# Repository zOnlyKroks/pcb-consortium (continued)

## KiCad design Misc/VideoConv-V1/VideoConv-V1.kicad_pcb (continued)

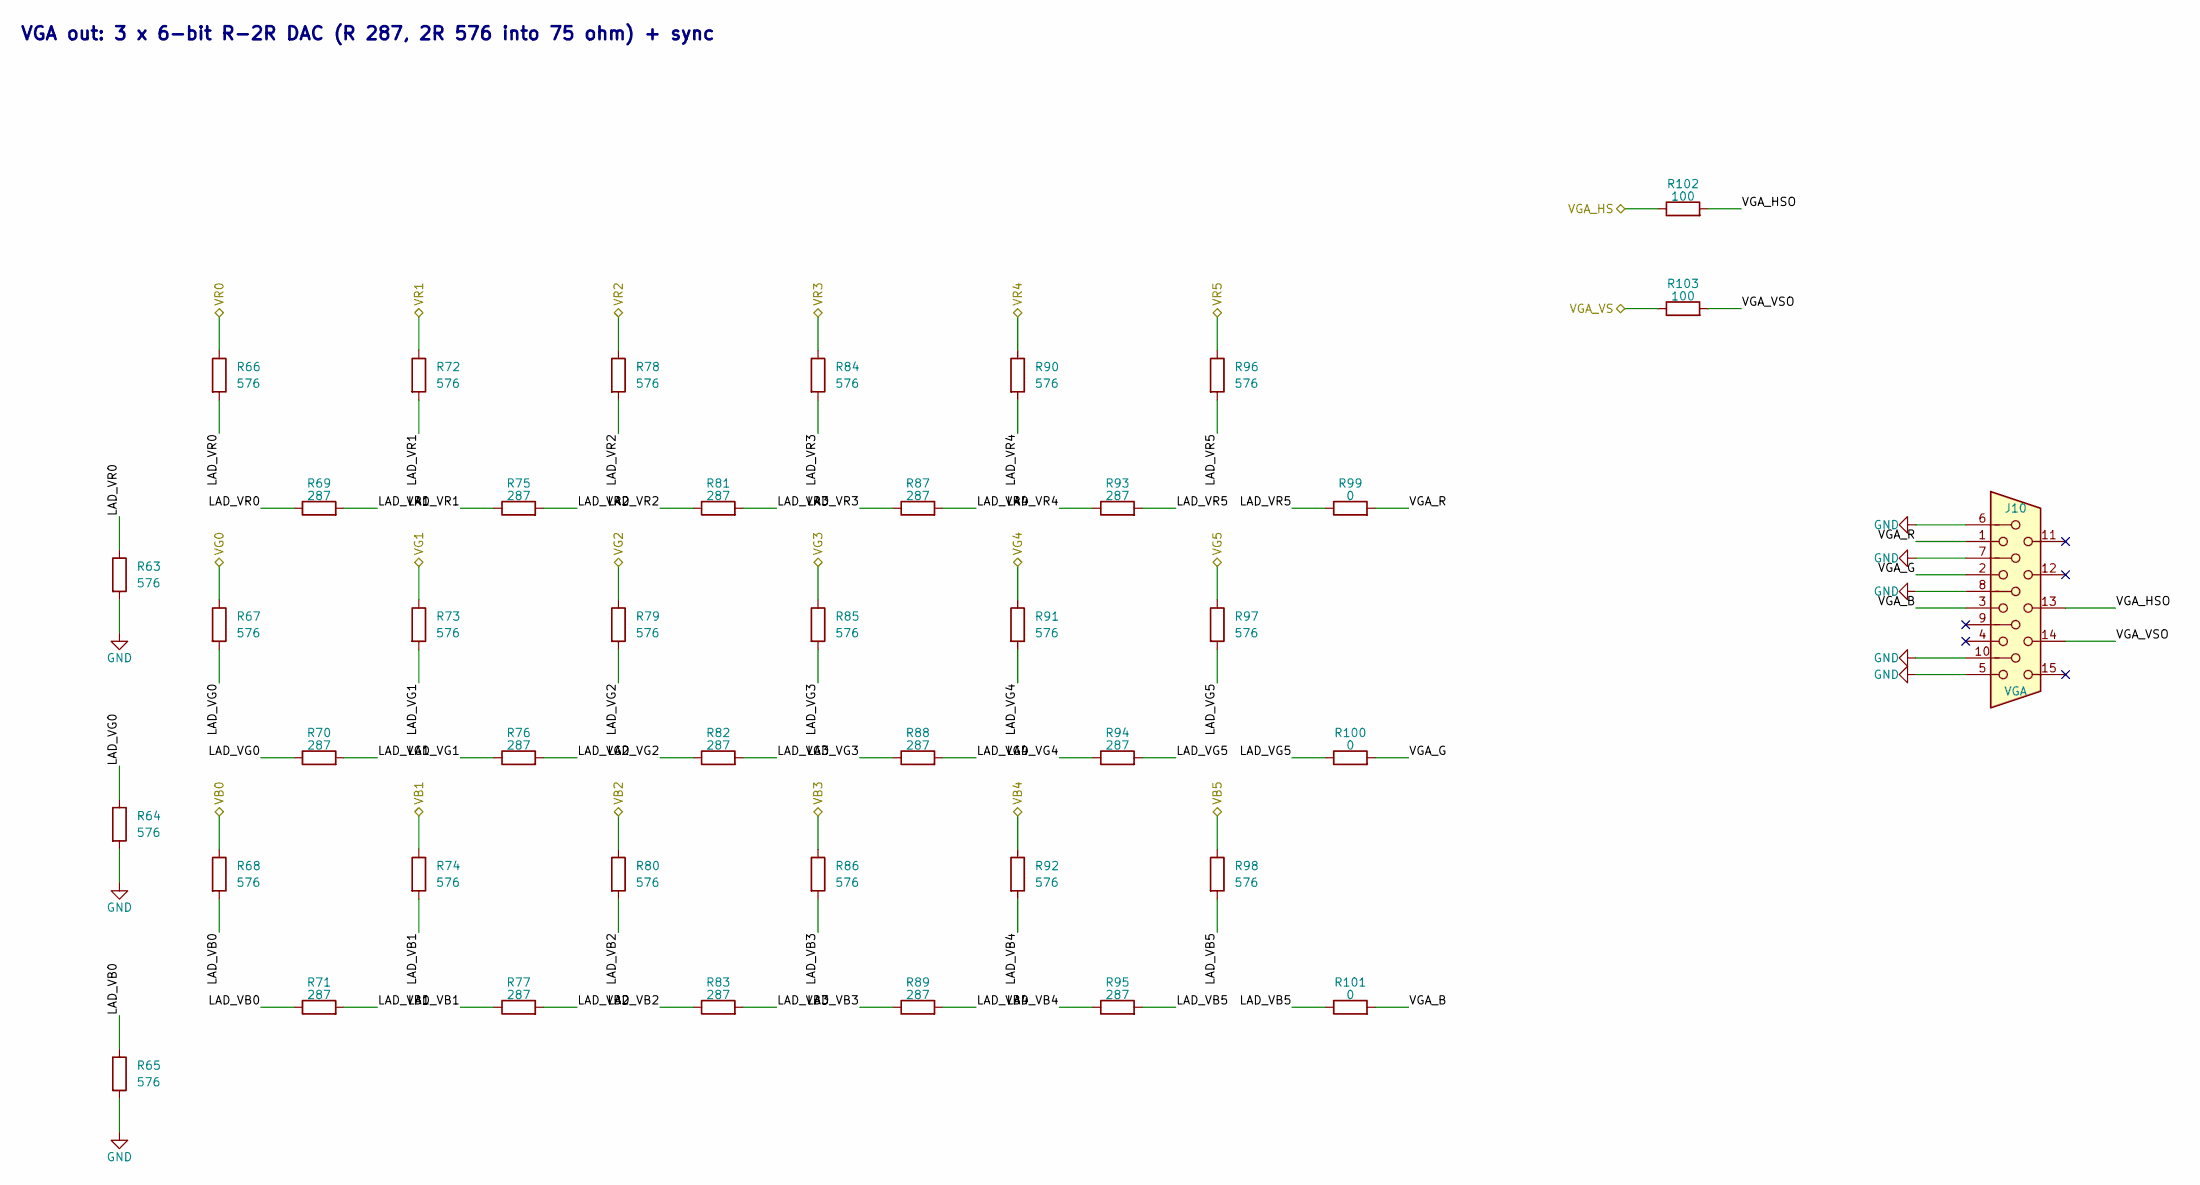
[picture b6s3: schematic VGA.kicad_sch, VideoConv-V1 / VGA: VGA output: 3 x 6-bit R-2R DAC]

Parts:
J10: VGA; DSUB-15-HD_Socket_Horizontal_P2.29x1.90mm_EdgePinOffset3.03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; LCSC Part # C5172168
R63, R64, R65, R66, R67, R68, R72, R73, R74, R78, R79, R80, R84, R85, R86, R90, R91, R92, R96, R97, R98: 576; R_0603_1608Metric; Tolerance 1%; LCSC Part # C245982
R69, R70, R71, R75, R76, R77, R81, R82, R83, R87, R88, R89, R93, R94, R95: 287; R_0603_1608Metric; Tolerance 1%; LCSC Part # C22929
R99, R100, R101: 0; R_0603_1608Metric; LCSC Part # C21189
R102, R103: 100; R_0603_1608Metric; LCSC Part # C22775

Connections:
/VB0: R68.1; also elsewhere on the board
/VB1: R74.1; also elsewhere on the board
/VB2: R80.1; also elsewhere on the board
/VB3: R86.1; also elsewhere on the board
/VB4: R92.1; also elsewhere on the board
/VB5: R98.1; also elsewhere on the board
/VG0: R67.1; also elsewhere on the board
/VG1: R73.1; also elsewhere on the board
/VG2: R79.1; also elsewhere on the board
/VG3: R85.1; also elsewhere on the board
/VG4: R91.1; also elsewhere on the board
/VG5: R97.1; also elsewhere on the board
/VGA/LAD_VB0: R65.1, R68.2, R71.1
/VGA/LAD_VB1: R71.2, R74.2, R77.1
/VGA/LAD_VB2: R77.2, R80.2, R83.1
/VGA/LAD_VB3: R83.2, R86.2, R89.1
/VGA/LAD_VB4: R89.2, R92.2, R95.1
/VGA/LAD_VB5: R95.2, R98.2, R101.1
/VGA/LAD_VG0: R64.1, R67.2, R70.1
/VGA/LAD_VG1: R70.2, R73.2, R76.1
/VGA/LAD_VG2: R76.2, R79.2, R82.1
/VGA/LAD_VG3: R82.2, R85.2, R88.1
/VGA/LAD_VG4: R88.2, R91.2, R94.1
/VGA/LAD_VG5: R94.2, R97.2, R100.1
/VGA/LAD_VR0: R63.1, R66.2, R69.1
/VGA/LAD_VR1: R69.2, R72.2, R75.1
/VGA/LAD_VR2: R75.2, R78.2, R81.1
/VGA/LAD_VR3: R81.2, R84.2, R87.1
/VGA/LAD_VR4: R87.2, R90.2, R93.1
/VGA/LAD_VR5: R93.2, R96.2, R99.1
/VGA/VGA_B: J10.3, R101.2
/VGA/VGA_G: J10.2, R100.2
/VGA/VGA_HSO: J10.13, R102.2
/VGA/VGA_R: J10.1, R99.2
/VGA/VGA_VSO: J10.14, R103.2
/VGA_HS: R102.1; also elsewhere on the board
/VGA_VS: R103.1; also elsewhere on the board
/VR0: R66.1; also elsewhere on the board
/VR1: R72.1; also elsewhere on the board
/VR2: R78.1; also elsewhere on the board
/VR3: R84.1; also elsewhere on the board
/VR4: R90.1; also elsewhere on the board
/VR5: R96.1; also elsewhere on the board
GND: J10.5, J10.6, J10.7, J10.8, J10.10, R63.2, R64.2, R65.2; also elsewhere on the board

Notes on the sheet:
VGA out: 3 x 6-bit R-2R DAC (R 287, 2R 576 into 75 ohm) + sync

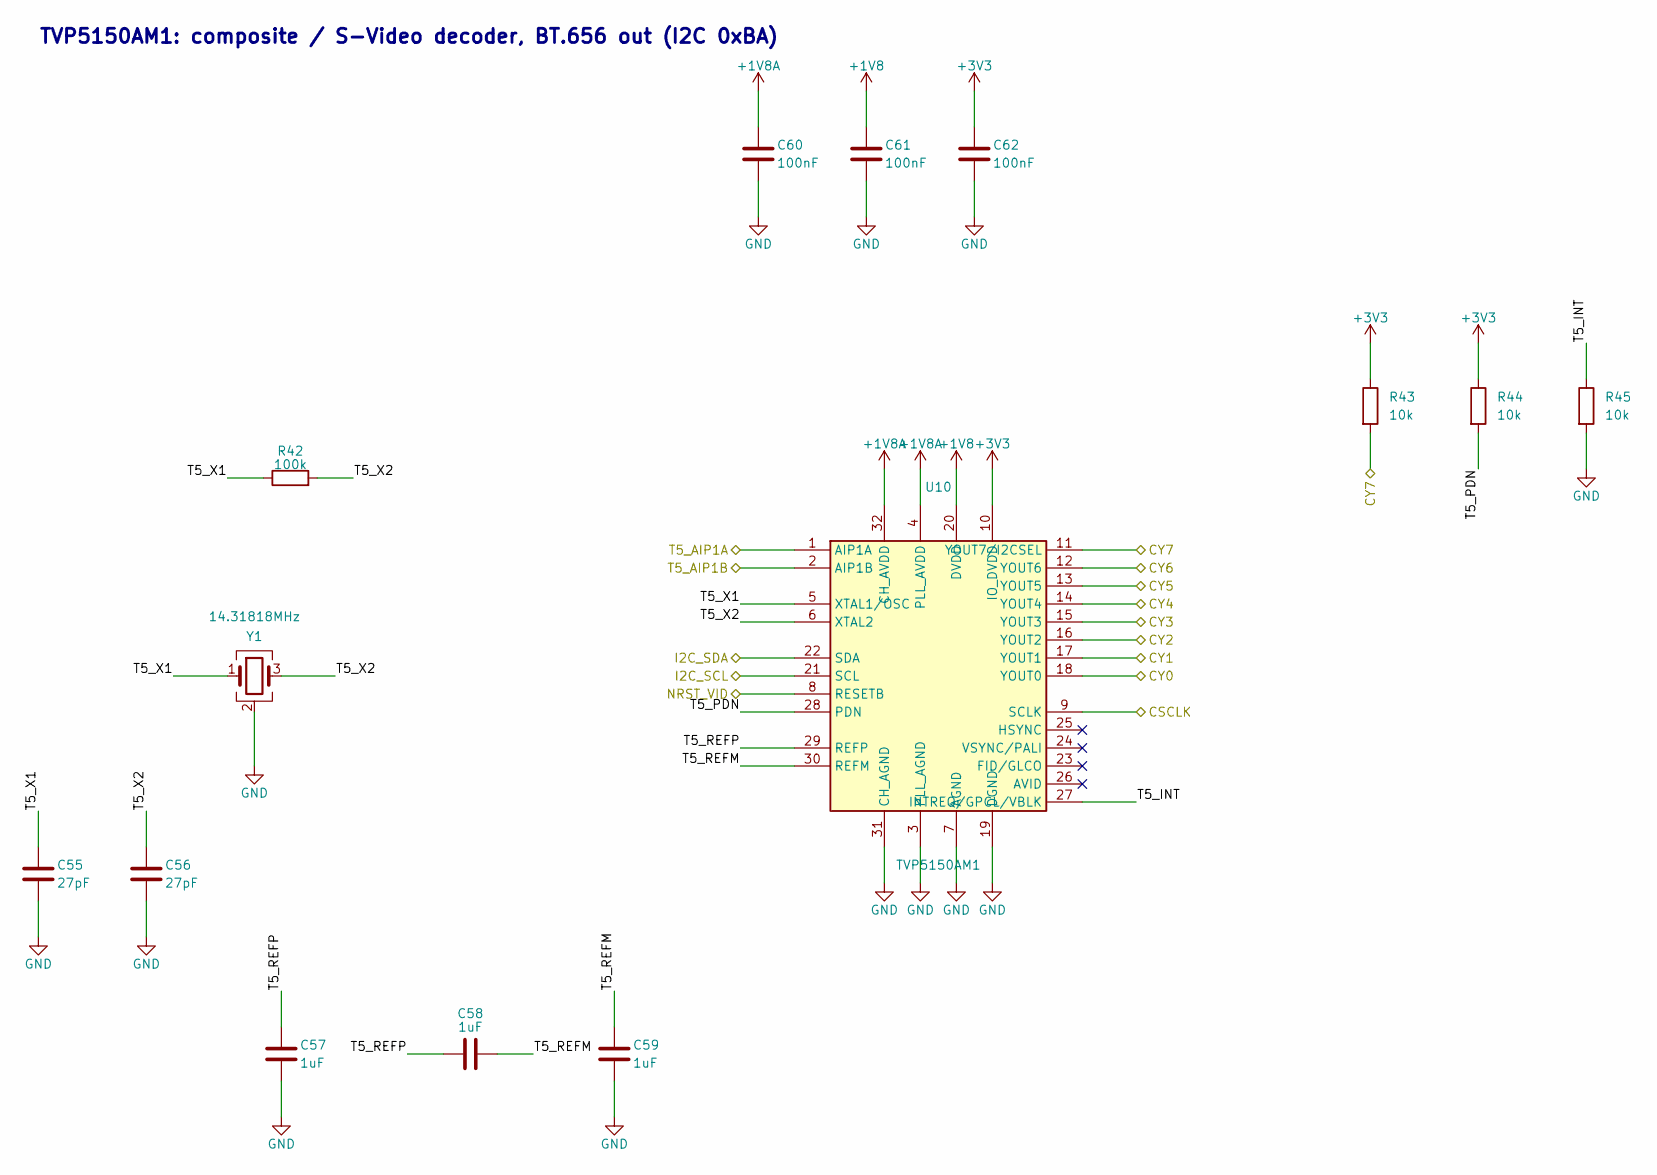
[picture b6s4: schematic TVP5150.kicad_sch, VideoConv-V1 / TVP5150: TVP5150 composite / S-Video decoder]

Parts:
C55, C56: 27pF; C_0603_1608Metric; LCSC Part # C1656
C57, C58, C59: 1uF; C_0603_1608Metric; LCSC Part # C29936
C60, C61, C62: 100nF; C_0603_1608Metric; LCSC Part # C1591
R42: 100k; R_0603_1608Metric; LCSC Part # C25803
R43, R44, R45: 10k; R_0603_1608Metric; LCSC Part # C25804
U10: TVP5150AM1; TQFP-32_7x7mm_P0.8mm; MPN TVP5150AM1PBS; LCSC Part # C3824301
Y1: 14.31818MHz; Crystal_SMD_3225-4Pin_3.2x2.5mm; LCSC Part # C6531315

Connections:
+1V8: C61.1, U10.20 (DVDD); also elsewhere on the board
+1V8A: C60.1, U10.4 (PLL_AVDD), U10.32 (CH_AVDD); also elsewhere on the board
+3V3: C62.1, R43.1, R44.1, U10.10 (IO_DVDD); also elsewhere on the board
/CSCLK: U10.9 (SCLK); also elsewhere on the board
/CY0: U10.18 (YOUT0); also elsewhere on the board
/CY1: U10.17 (YOUT1); also elsewhere on the board
/CY2: U10.16 (YOUT2); also elsewhere on the board
/CY3: U10.15 (YOUT3); also elsewhere on the board
/CY4: U10.14 (YOUT4); also elsewhere on the board
/CY5: U10.13 (YOUT5); also elsewhere on the board
/CY6: U10.12 (YOUT6); also elsewhere on the board
/CY7: R43.2, U10.11 (YOUT7/I2CSEL); also elsewhere on the board
/I2C_SCL: U10.21 (SCL); also elsewhere on the board
/I2C_SDA: U10.22 (SDA); also elsewhere on the board
/NRST_VID: U10.8 (RESETB); also elsewhere on the board
/T5_AIP1A: U10.1 (AIP1A); also elsewhere on the board
/T5_AIP1B: U10.2 (AIP1B); also elsewhere on the board
/TVP5150/T5_INT: R45.1, U10.27 (INTREQ/GPCL/VBLK)
/TVP5150/T5_PDN: R44.2, U10.28 (PDN)
/TVP5150/T5_REFM: C58.2, C59.1, U10.30 (REFM)
/TVP5150/T5_REFP: C57.1, C58.1, U10.29 (REFP)
/TVP5150/T5_X1: C55.1, R42.1, U10.5 (XTAL1/OSC), Y1.1
/TVP5150/T5_X2: C56.1, R42.2, U10.6 (XTAL2), Y1.3
GND: C55.2, C56.2, C57.2, C59.2, C60.2, C61.2, C62.2, R45.2, U10.3 (PLL_AGND), U10.7 (AGND), U10.19 (DGND), U10.31 (CH_AGND), Y1.2 (G), Y1.4 (G); also elsewhere on the board

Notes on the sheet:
TVP5150AM1: composite / S-Video decoder, BT.656 out (I2C 0xBA)

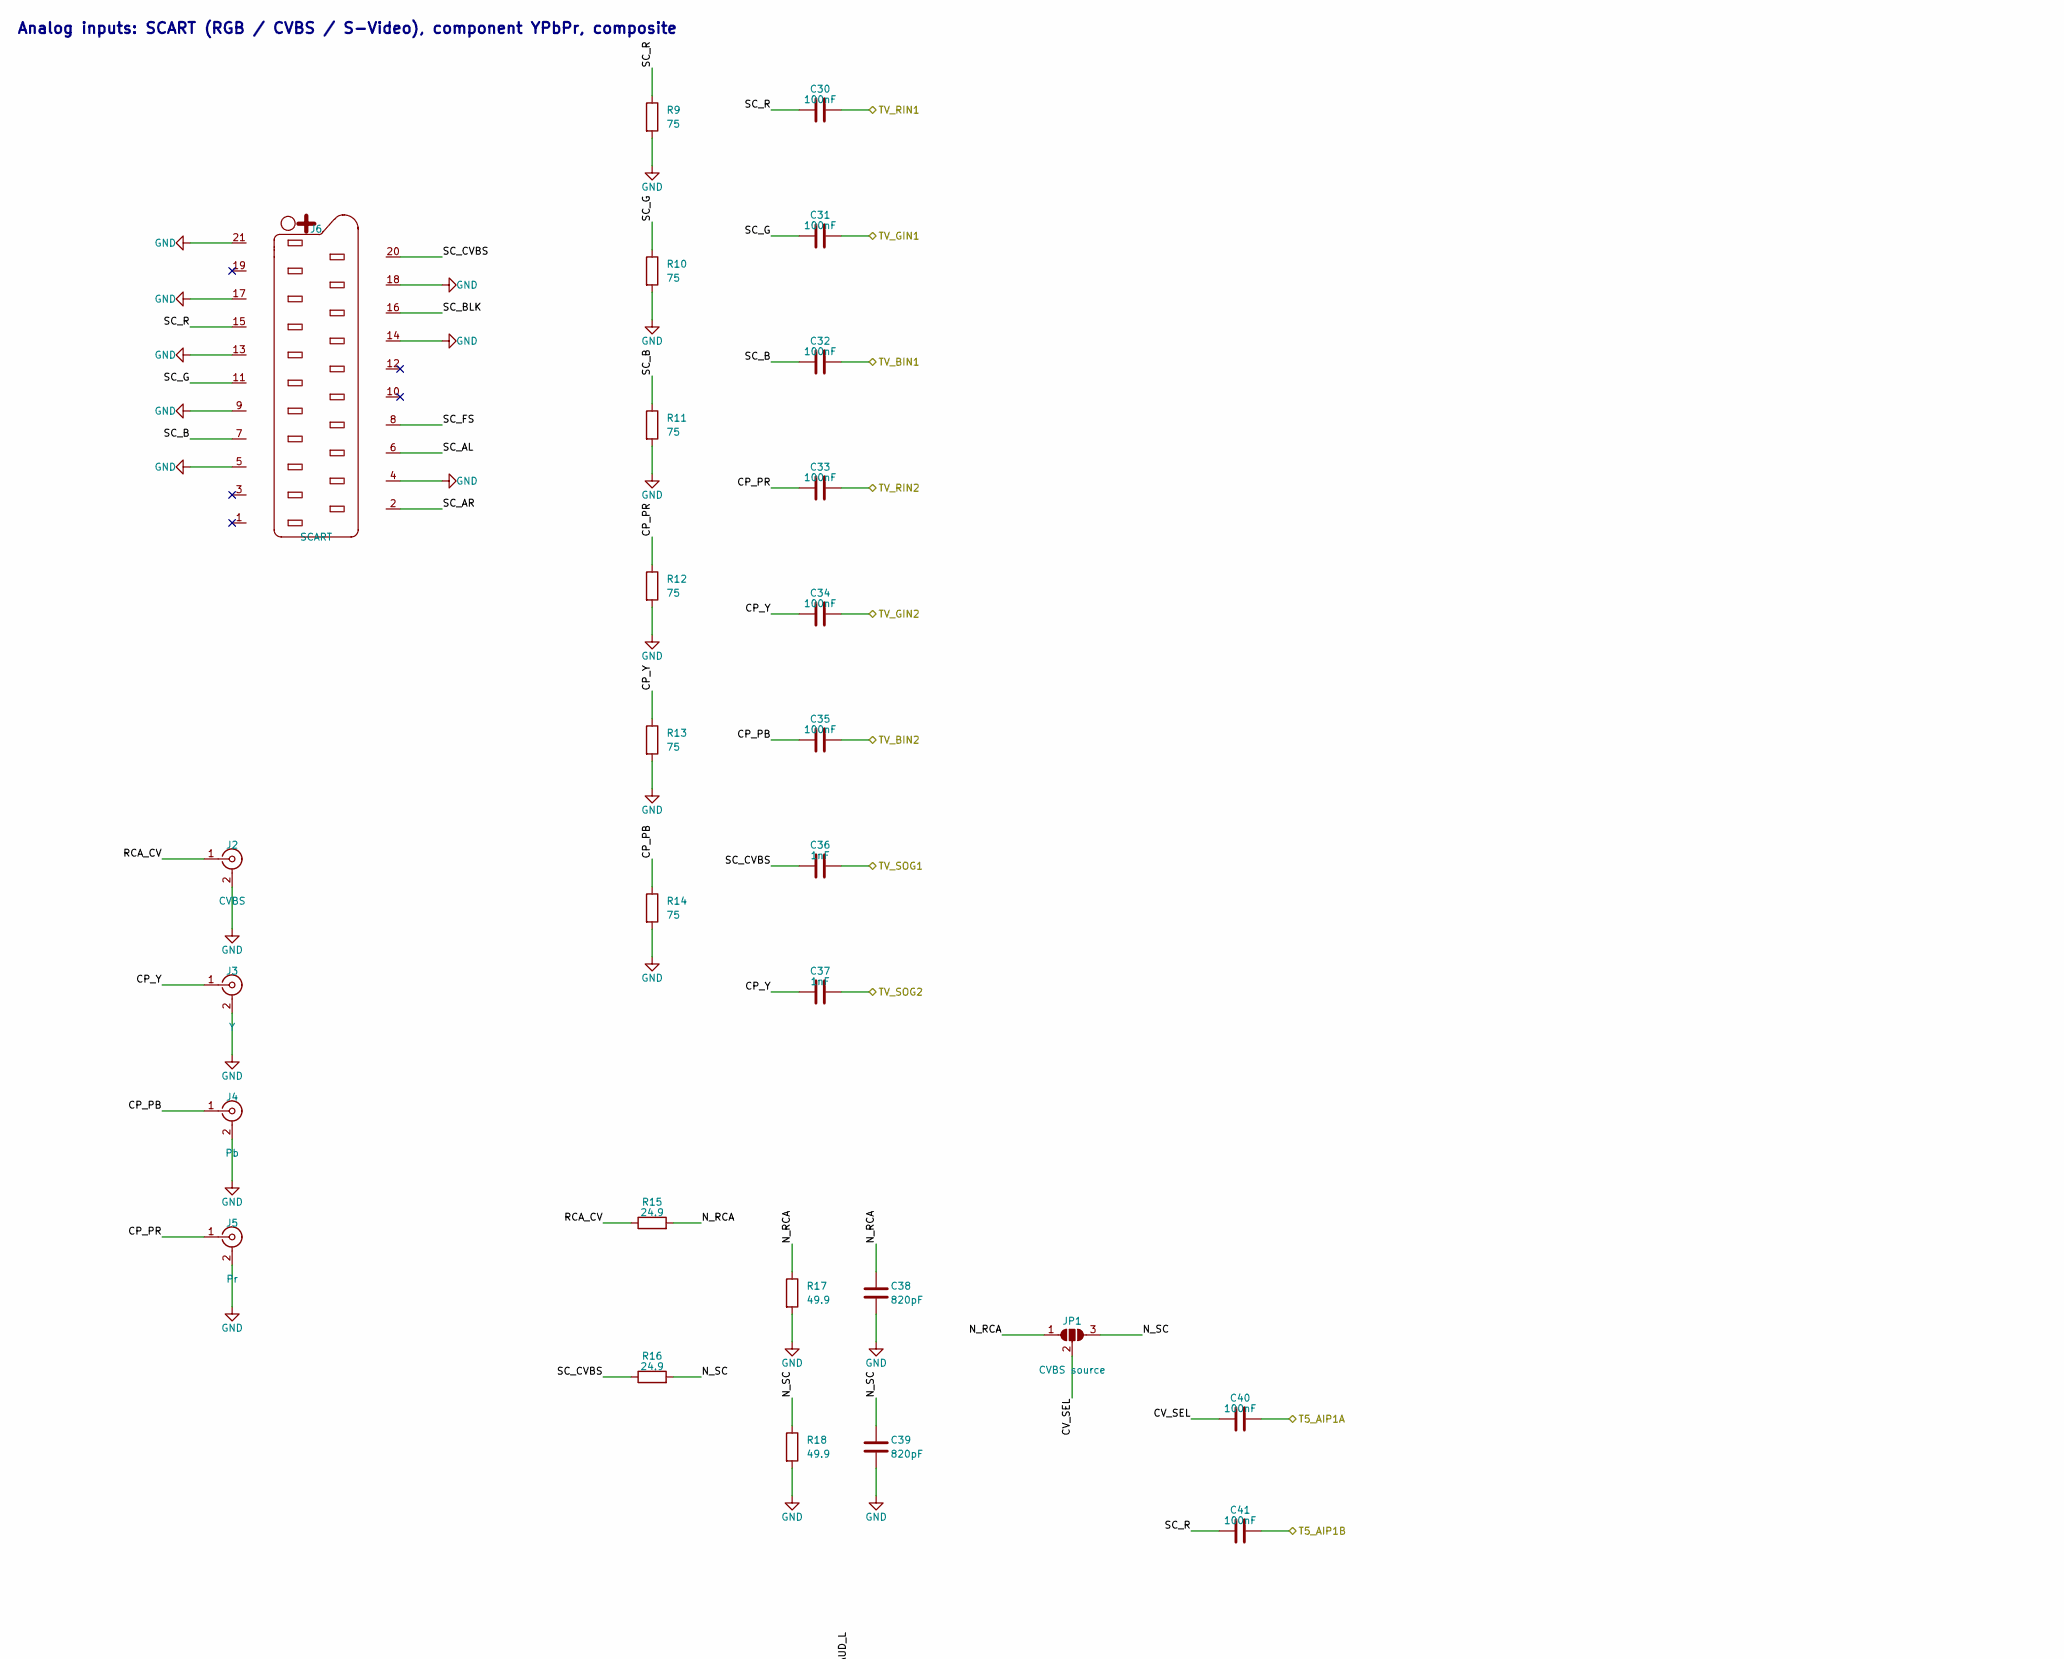
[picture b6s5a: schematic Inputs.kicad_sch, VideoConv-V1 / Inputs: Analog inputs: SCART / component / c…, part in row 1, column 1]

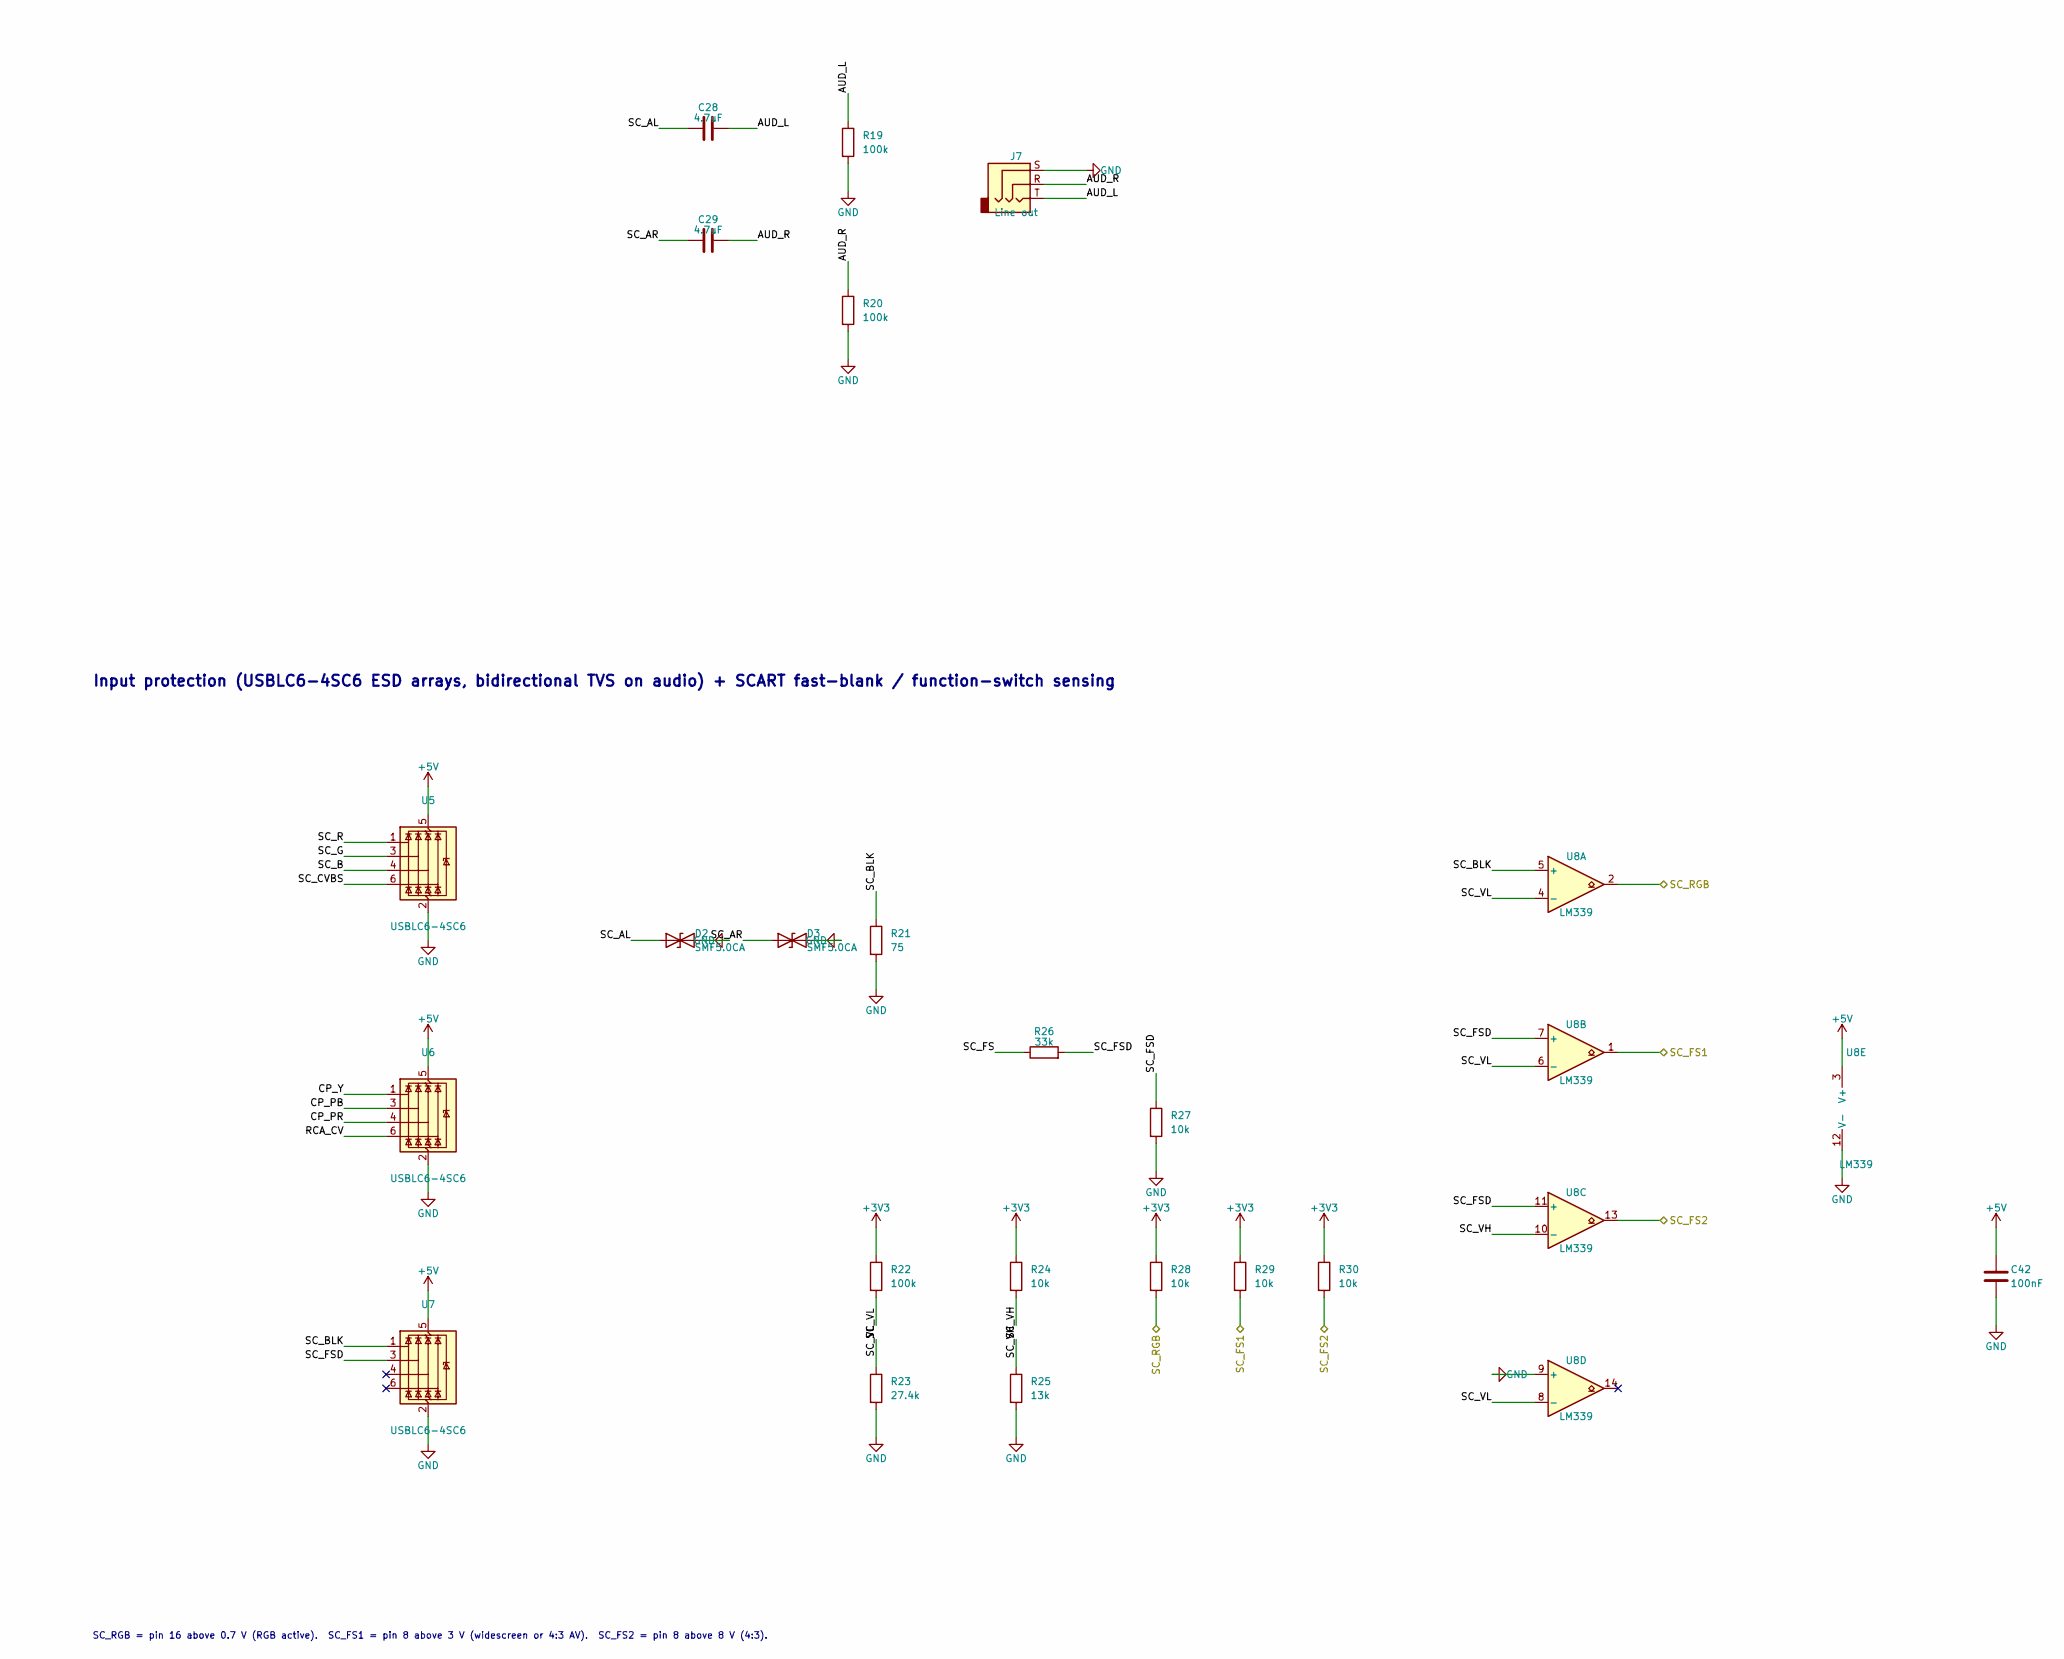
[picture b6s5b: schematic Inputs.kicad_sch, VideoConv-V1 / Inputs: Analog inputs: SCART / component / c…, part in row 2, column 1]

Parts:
C28, C29: 4.7uF; C_0805_2012Metric; LCSC Part # C1746
C30, C31, C32, C33, C34, C35, C40, C41, C42: 100nF; C_0603_1608Metric; LCSC Part # C1591
C36, C37: 1nF; C_0603_1608Metric; LCSC Part # C1588
C38, C39: 820pF; C_0603_1608Metric; LCSC Part # C307512
D2, D3: SMF5.0CA; D_SOD-123; LCSC Part # C364279
J2: CVBS; RCA_XDJK-0271-1650; LCSC Part # C7527522
J3: Y; RCA_XDJK-0271-1650; LCSC Part # C7527522
J4: Pb; RCA_XDJK-0271-1650; LCSC Part # C7527522
J5: Pr; RCA_XDJK-0271-1650; LCSC Part # C7527522
J6: SCART; SCART_Kycon_K-SCART-021; MPN 21-pin right-angle PCB SCART socket (Ky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
J7: Line out; Jack_3.5mm_PJ-307N5_Horizontal; MPN PJ-307N5; LCSC Part # C692542
JP1: CVBS source; SolderJumper-3_P1.3mm_Open_Pad1.0x1.5mm
R9, R10, R11, R12, R13, R14, R21: 75; R_0603_1608Metric; Tolerance 1%; LCSC Part # C4275
R15, R16: 24.9; R_0603_1608Metric; Tolerance 1%; LCSC Part # C22916
R17, R18: 49.9; R_0603_1608Metric; Tolerance 1%; LCSC Part # C23185
R19, R20, R22: 100k; R_0603_1608Metric; LCSC Part # C25803
R23: 27.4k; R_0603_1608Metric; Tolerance 1%; LCSC Part # C22964
R24, R27, R28, R29, R30: 10k; R_0603_1608Metric; LCSC Part # C25804
R25: 13k; R_0603_1608Metric; Tolerance 1%; LCSC Part # C22797
R26: 33k; R_0603_1608Metric; LCSC Part # C4216
U5, U6, U7: USBLC6-4SC6; SOT-23-6; MPN USBLC6-4SC6; LCSC Part # C111212
U8: LM339; SOIC-14_3.9x8.7mm_P1.27mm; MPN LM339DR; LCSC Part # C7948

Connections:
+3V3: R22.1, R24.1, R28.1, R29.1, R30.1; also elsewhere on the board
+5V: C42.1, U5.5 (VBUS), U6.5 (VBUS), U7.5 (VBUS), U8.3 (V+); also elsewhere on the board
/Inputs/AUD_L: C28.2, J7.T, R19.1
/Inputs/AUD_R: C29.2, J7.R, R20.1
/Inputs/CP_PB: C35.1, J4.1 (In), R14.1, U6.3 (I/O2)
/Inputs/CP_PR: C33.1, J5.1 (In), R12.1, U6.4 (I/O3)
/Inputs/CP_Y: C34.1, C37.1, J3.1 (In), R13.1, U6.1 (I/O1)
/Inputs/CV_SEL: C40.1, JP1.2 (C)
/Inputs/N_RCA: C38.1, JP1.1 (A), R15.2, R17.1
/Inputs/N_SC: C39.1, JP1.3 (B), R16.2, R18.1
/Inputs/RCA_CV: J2.1 (In), R15.1, U6.6 (I/O4)
/Inputs/SC_AL: C28.1, D2.1 (A1), J6.6
/Inputs/SC_AR: C29.1, D3.1 (A1), J6.2
/Inputs/SC_B: C32.1, J6.7, R11.1, U5.4 (I/O3)
/Inputs/SC_BLK: J6.16, R21.1, U7.1 (I/O1), U8.5 (+)
/Inputs/SC_CVBS: C36.1, J6.20, R16.1, U5.6 (I/O4)
/Inputs/SC_FS: J6.8, R26.1
/Inputs/SC_FSD: R26.2, R27.1, U7.3 (I/O2), U8.7 (+), U8.11 (+)
/Inputs/SC_G: C31.1, J6.11, R10.1, U5.3 (I/O2)
/Inputs/SC_R: C30.1, C41.1, J6.15, R9.1, U5.1 (I/O1)
/Inputs/SC_VH: R24.2, R25.1, U8.10 (-)
/Inputs/SC_VL: R22.2, R23.1, U8.4 (-), U8.6 (-), U8.8 (-)
/SC_FS1: R29.2, U8.1; also elsewhere on the board
/SC_FS2: R30.2, U8.13; also elsewhere on the board
/SC_RGB: R28.2, U8.2; also elsewhere on the board
/T5_AIP1A: C40.2; also elsewhere on the board
/T5_AIP1B: C41.2; also elsewhere on the board
/TV_BIN1: C32.2; also elsewhere on the board
/TV_BIN2: C35.2; also elsewhere on the board
/TV_GIN1: C31.2; also elsewhere on the board
/TV_GIN2: C34.2; also elsewhere on the board
/TV_RIN1: C30.2; also elsewhere on the board
/TV_RIN2: C33.2; also elsewhere on the board
/TV_SOG1: C36.2; also elsewhere on the board
/TV_SOG2: C37.2; also elsewhere on the board
GND: C38.2, C39.2, C42.2, D2.2 (A2), D3.2 (A2), J2.2 (Ext), J3.2 (Ext), J4.2 (Ext), J5.2 (Ext), J6.4, J6.5, J6.9, J6.13, J6.14, J6.17, J6.18, J6.21, J7.S, R9.2, R10.2, R11.2, R12.2, R13.2, R14.2, R17.2, R18.2, R19.2, R20.2, R21.2, R23.2, R25.2, R27.2, U5.2 (GND), U6.2 (GND), U7.2 (GND), U8.9 (+), U8.12 (V-); also elsewhere on the board

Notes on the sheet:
Analog inputs: SCART (RGB / CVBS / S-Video), component YPbPr, composite
SC_RGB = pin 16 above 0.7 V (RGB active). SC_FS1 = pin 8 above 3 V (widescreen or 4:3 AV). SC_FS2 = pin 8 above 8 V (4:3).
Input protection (USBLC6-4SC6 ESD arrays, bidirectional TVS on audio) + SCART fast-blank / function-switch sensing

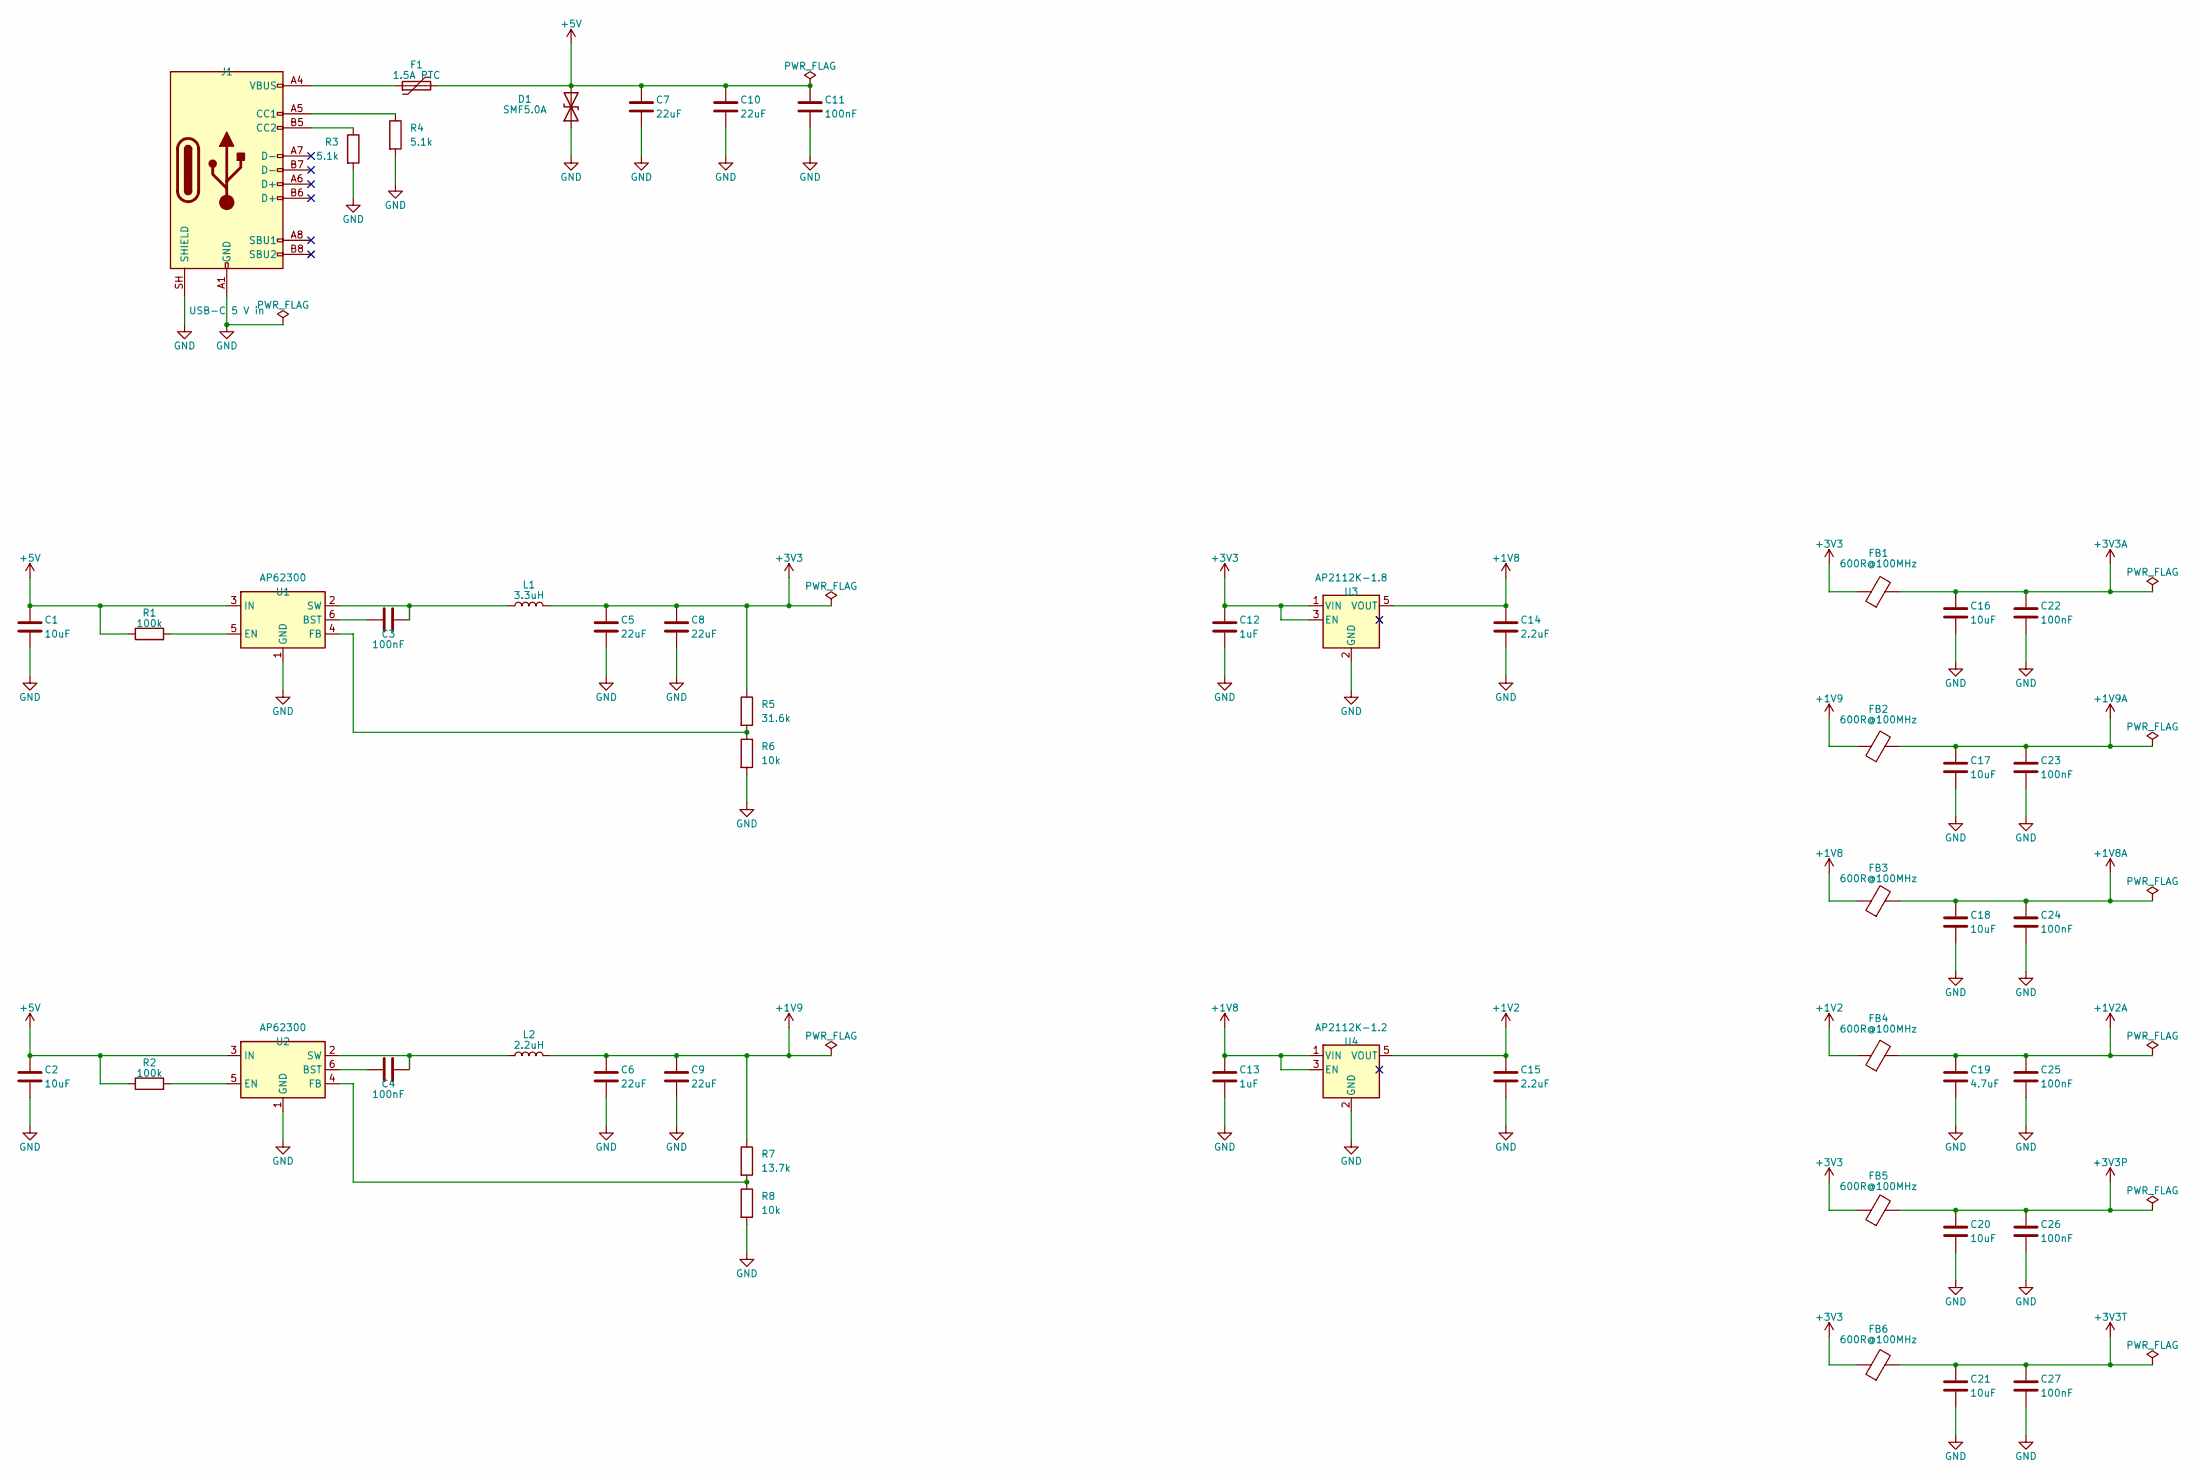
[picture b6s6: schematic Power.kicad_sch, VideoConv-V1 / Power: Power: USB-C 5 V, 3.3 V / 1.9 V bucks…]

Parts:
C1, C2, C16, C17, C18, C20, C21: 10uF; C_0805_2012Metric; LCSC Part # C15850
C3, C4, C11, C22, C23, C24, C25, C26, C27: 100nF; C_0603_1608Metric; LCSC Part # C1591
C5, C6, C7, C8, C9, C10: 22uF; C_1206_3216Metric; LCSC Part # C12891
C12, C13: 1uF; C_0603_1608Metric; LCSC Part # C29936
C14, C15: 2.2uF; C_0603_1608Metric; LCSC Part # C23630
C19: 4.7uF; C_0805_2012Metric; LCSC Part # C1746
D1: SMF5.0A; D_SOD-123; LCSC Part # C193402
F1: 1.5A PTC; Fuse_1206_3216Metric; MPN hold 1.5 A, 6 V; LCSC Part # C49318384
FB1, FB2, FB3, FB4, FB5, FB6: 600R@100MHz; L_0805_2012Metric; LCSC Part # C85837
J1: USB-C 5 V in; USB_C_Receptacle_HRO_TYPE-C-31-M-12; LCSC Part # C165948
L1: 3.3uH; L_Bourns-SRN6028; LCSC Part # C528022
L2: 2.2uH; L_Bourns-SRN6028; LCSC Part # C168025
R1, R2: 100k; R_0603_1608Metric; LCSC Part # C25803
R3, R4: 5.1k; R_0603_1608Metric; LCSC Part # C23186
R5: 31.6k; R_0603_1608Metric; Tolerance 1%; LCSC Part # C25967
R6, R8: 10k; R_0603_1608Metric; Tolerance 1%; LCSC Part # C25804
R7: 13.7k; R_0603_1608Metric; Tolerance 1%; LCSC Part # C22793
U1, U2: AP62300; TSOT-23-6; MPN AP62300WU-7; LCSC Part # C1880390
U3: AP2112K-1.8; SOT-23-5; MPN AP2112K-1.8; LCSC Part # C176944
U4: AP2112K-1.2; SOT-23-5; MPN AP2112K-1.2; LCSC Part # C460310

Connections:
+1V2: C15.1, FB4.1, U4.5 (VOUT); also elsewhere on the board
+1V2A: C19.1, C25.1, FB4.2; also elsewhere on the board
+1V8: C13.1, C14.1, FB3.1, U3.5 (VOUT), U4.1 (VIN), U4.3 (EN); also elsewhere on the board
+1V8A: C18.1, C24.1, FB3.2; also elsewhere on the board
+1V9: C6.1, C9.1, FB2.1, L2.2, R7.1; also elsewhere on the board
+1V9A: C17.1, C23.1, FB2.2; also elsewhere on the board
+3V3: C5.1, C8.1, C12.1, FB1.1, FB5.1, FB6.1, L1.2, R5.1, U3.1 (VIN), U3.3 (EN); also elsewhere on the board
+3V3A: C16.1, C22.1, FB1.2; also elsewhere on the board
+3V3P: C20.1, C26.1, FB5.2; also elsewhere on the board
+3V3T: C21.1, C27.1, FB6.2; also elsewhere on the board
+5V: C1.1, C2.1, C7.1, C10.1, C11.1, D1.2 (A2), F1.2, R1.1, R2.1, U1.3 (IN), U2.3 (IN); also elsewhere on the board
GND: C1.2, C2.2, C5.2, C6.2, C7.2, C8.2, C9.2, C10.2, C11.2, C12.2, C13.2, C14.2, C15.2, C16.2, C17.2, C18.2, C19.2, C20.2, C21.2, C22.2, C23.2, C24.2, C25.2, C26.2, C27.2, D1.1 (A1), J1.A1 (GND), J1.A12 (GND), J1.B1 (GND), J1.B12 (GND), J1.SH (SHIELD), R3.2, R4.2, R6.2, R8.2, U1.1 (GND), U2.1 (GND), U3.2 (GND), U4.2 (GND); also elsewhere on the board
unnamed: F1.1, J1.A4 (VBUS), J1.A9 (VBUS), J1.B4 (VBUS), J1.B9 (VBUS)
unnamed: J1.A5 (CC1), R4.1
unnamed: J1.B5 (CC2), R3.1
unnamed: C3.1, U1.6 (BST)
unnamed: R1.2, U1.5 (EN)
unnamed: R5.2, R6.1, U1.4 (FB)
unnamed: C3.2, L1.1, U1.2 (SW)
unnamed: C4.1, U2.6 (BST)
unnamed: R2.2, U2.5 (EN)
unnamed: R7.2, R8.1, U2.4 (FB)
unnamed: C4.2, L2.1, U2.2 (SW)
